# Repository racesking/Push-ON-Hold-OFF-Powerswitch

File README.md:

# Push-ON Hold-OFF Powerswitch
 SImple circuit to enable power switching for microcontrollers and small devices

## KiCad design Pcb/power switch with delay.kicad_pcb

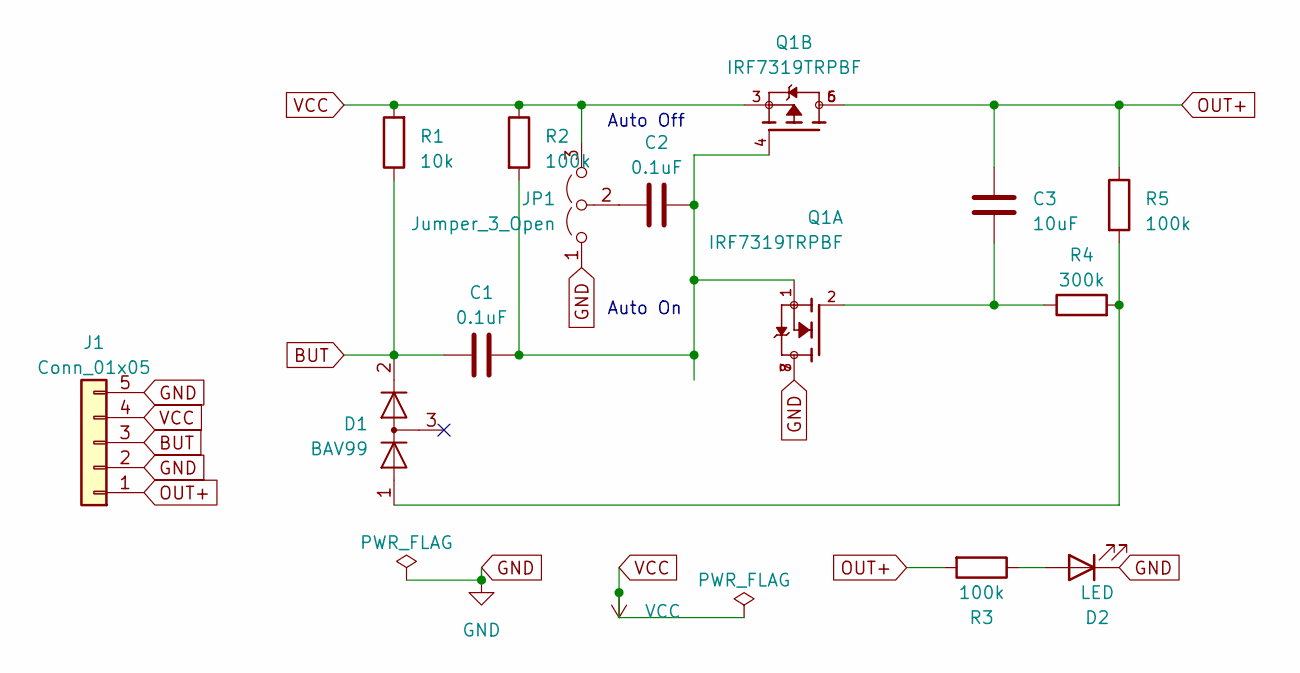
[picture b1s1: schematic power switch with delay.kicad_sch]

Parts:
C1, C2: 0.1uF; CP_EIA-2012-12_Kemet-R_Pad1.30x1.05mm_HandSolder
C3: 10uF; CP_EIA-2012-12_Kemet-R_Pad1.30x1.05mm_HandSolder
D1: BAV99; SOT-23
D2: LED; LED_0805_2012Metric
J1: Conn_01x05; PinHeader_1x05_P2.54mm_Vertical
JP1: Jumper_3_Open; SolderJumper-3_P1.3mm_Open_RoundedPad1.0x1.5mm_NumberLabels
Q1: IRF7319TRPBF; Diodes_PSOP-8
R1: 10k; R_0805_2012Metric
R2, R3, R5: 100k; R_0805_2012Metric
R4: 300k; R_0805_2012Metric

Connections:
BUT: C1.1, D1.2 (A), J1.3, R1.1
GND: D2.1 (K), J1.2, J1.5, JP1.1 (A), Q1.7, Q1.8
unnamed: C1.2, C2.2, Q1.1, Q1.4, R2.2
unnamed: C3.2, Q1.2, R4.1
unnamed: D1.1 (K), R4.2, R5.2
unnamed: D2.2 (A), R3.1
unnamed: C2.1, JP1.2 (C)
OUT+: C3.1, J1.1, Q1.5, Q1.6, R3.2, R5.1
VCC: J1.4, JP1.3 (B), Q1.3, R1.2, R2.1

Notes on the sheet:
Auto Off
Auto On

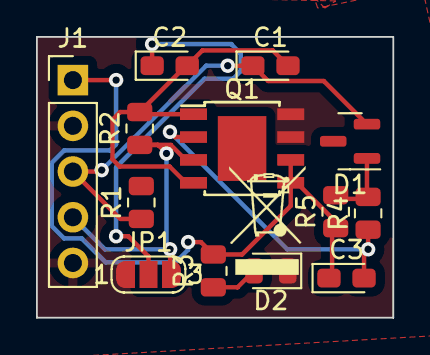
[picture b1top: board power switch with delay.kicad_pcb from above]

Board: 2 copper layers, 19.8 x 15.6 mm, 13 parts (0 on the bottom side), 9 nets.

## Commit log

2023-05-02 Initial commit
    Kicad project with gerber files
